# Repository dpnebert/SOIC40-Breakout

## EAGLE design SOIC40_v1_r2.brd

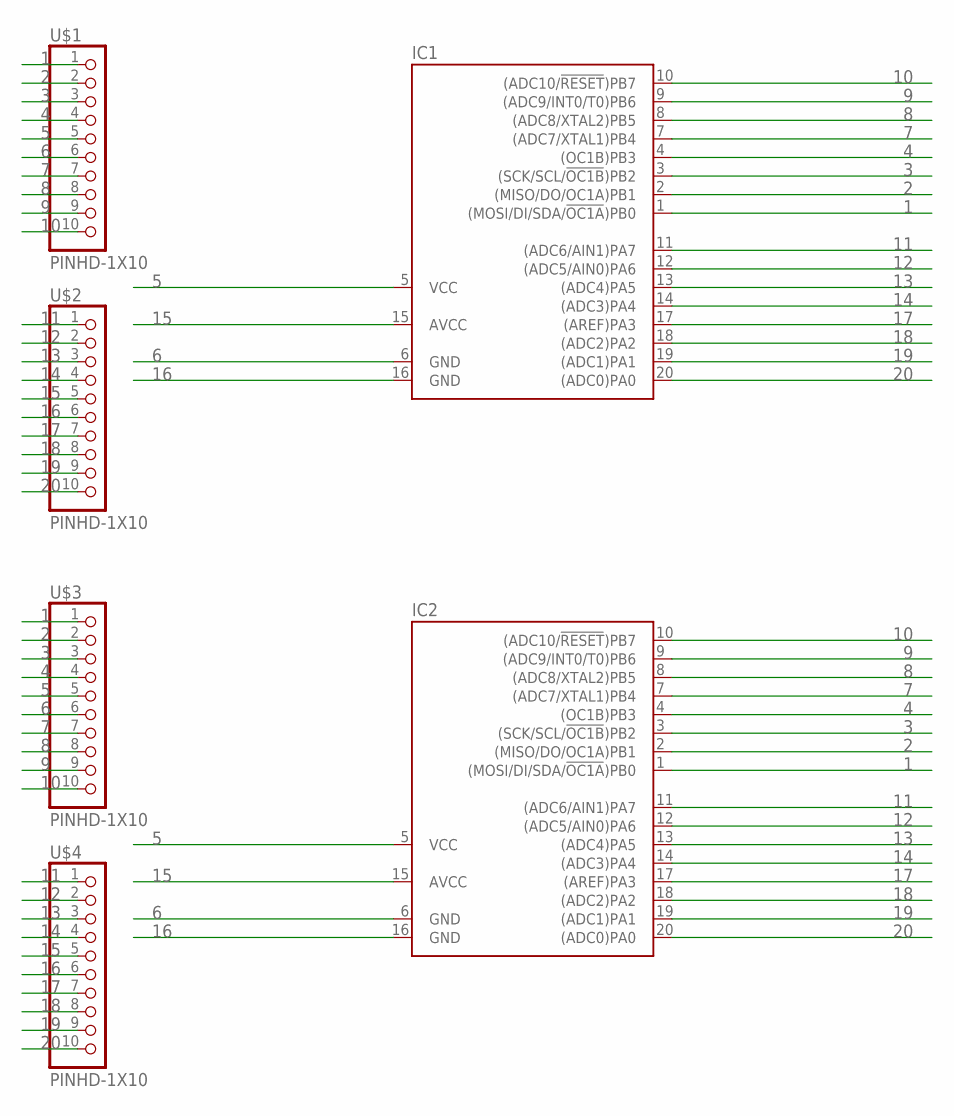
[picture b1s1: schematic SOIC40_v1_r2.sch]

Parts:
IC1, IC2: TINY26LS; SO20L
U$1, U$2, U$3, U$4: PINHD-1X10; 1X10-BIG

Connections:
1: IC1.1 ((MOSI/DI/SDA/!OC1A!)PB0), IC2.1 ((MOSI/DI/SDA/!OC1A!)PB0), U$1.1, U$3.1
2: IC1.2 ((MISO/DO/OC1A)PB1), IC2.2 ((MISO/DO/OC1A)PB1), U$1.2, U$3.2
3: IC1.3 ((SCK/SCL/!OC1B!)PB2), IC2.3 ((SCK/SCL/!OC1B!)PB2), U$1.3, U$3.3
4: IC1.4 ((OC1B)PB3), IC2.4 ((OC1B)PB3), U$1.4, U$3.4
5: IC1.5 (VCC), IC2.5 (VCC), U$1.5, U$3.5
6: IC1.6 (GND), IC2.6 (GND), U$1.6, U$3.6
7: IC1.7 ((ADC7/XTAL1)PB4), IC2.7 ((ADC7/XTAL1)PB4), U$1.7, U$3.7
8: IC1.8 ((ADC8/XTAL2)PB5), IC2.8 ((ADC8/XTAL2)PB5), U$1.8, U$3.8
9: IC1.9 ((ADC9/INT0/T0)PB6), IC2.9 ((ADC9/INT0/T0)PB6), U$1.9, U$3.9
10: IC1.10 ((ADC10/!RESET!)PB7), IC2.10 ((ADC10/!RESET!)PB7), U$1.10, U$3.10
11: IC1.11 ((ADC6/AIN1)PA7), IC2.11 ((ADC6/AIN1)PA7), U$2.1, U$4.1
12: IC1.12 ((ADC5/AIN0)PA6), IC2.12 ((ADC5/AIN0)PA6), U$2.2, U$4.2
13: IC1.13 ((ADC4)PA5), IC2.13 ((ADC4)PA5), U$2.3, U$4.3
14: IC1.14 ((ADC3)PA4), IC2.14 ((ADC3)PA4), U$2.4, U$4.4
15: IC1.15 (AVCC), IC2.15 (AVCC), U$2.5, U$4.5
16: IC1.16 (GND), IC2.16 (GND), U$2.6, U$4.6
17: IC1.17 ((AREF)PA3), IC2.17 ((AREF)PA3), U$2.7, U$4.7
18: IC1.18 ((ADC2)PA2), IC2.18 ((ADC2)PA2), U$2.8, U$4.8
19: IC1.19 ((ADC1)PA1), IC2.19 ((ADC1)PA1), U$2.9, U$4.9
20: IC1.20 ((ADC0)PA0), IC2.20 ((ADC0)PA0), U$2.10, U$4.10

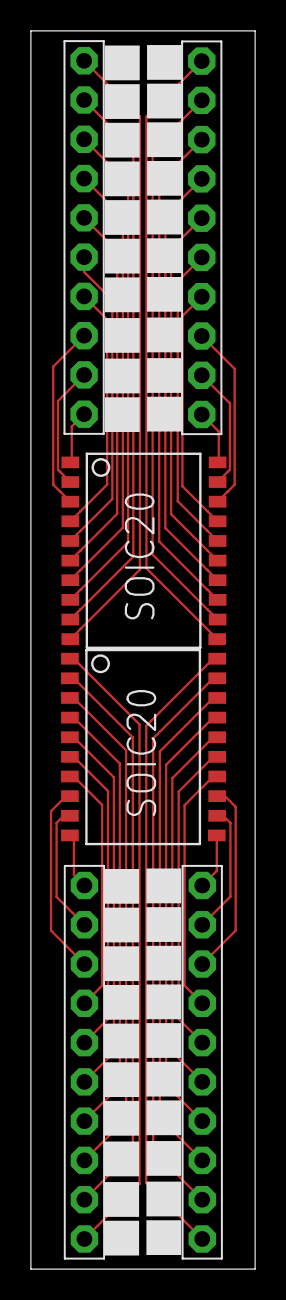
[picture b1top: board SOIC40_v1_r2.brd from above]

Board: 2 copper layers, 14.5 x 80.1 mm, 6 parts (0 on the bottom side), 20 nets.
